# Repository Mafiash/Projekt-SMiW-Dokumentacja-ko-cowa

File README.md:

# Smart LED - Inteligentny Sysytem Oświetlenia LED

**Autor:** Mateusz Smuda
**Sekcja:** 10 
**Nr albumu:** 312441 
**Rok:** 2025 

## Opis Projektu
Projekt "Smart LED" to system automatycznego sterowania oświetleniem LED WS2812B opartym na mikrokontrolerze ESP32-WROOM-32E. System wykorzystuje zaawansowany radar obecności (LD2410C) zamiast tradycyjnych czujników PIR. Dodatkowo barwa światła dostosowuje się do temperatury otoczenia przy użyciu czujnika DHT22, a jasność świecenia jest regulowana automatycznie w zależności od jasności otoczenia za pomocą fotorezystora.

Układ zarządzany jest przez własny serwer WWW postawiony na ESP32, umożliwiający zdalne sterowanie z poziomu przeglądarki (telefon/komputer).

## Główne Funkcjonalności
- **Wykrywanie obecności:** Radar LD2410C (wykrywanie ruchu i bezruchu).
- **Adaptacja barwna:** Zmiana koloru LED w zależności od temperatury (Niebieski <20°C / Zielony / Czerwony >26°C).
- **Adaptacja jasności:** Automatyczne ściemnianie w nocy i rozjaśnianie w dzień.
- **Interfejs WWW:** Panel sterowania (HTML/JS) z podglądem parametrów na żywo.
- **Tryby pracy:** 
  - **AUTO:** Pełna automatyka sensorowa.
  - **MANUAL:** Ręczne ustawianie koloru (RGB) i jasności suwakiem.

## Wykorzystany Sprzęt
1. **Mikrokontroler:** ESP32-WROOM-32E
2. **Oświetlenie:** Taśma LED adresowalna WS2812B (60 diod)
3. **Sensor ruchu:** Radar HLK-LD2410C
4. **Sensor temp/wilg:** DHT22
5. **Sensor światła:** Moduł z fotorezystorem

## Technologie
- **Język:** C++ (Arduino IDE)
- **Web:** HTML, CSS, JavaScript
- **Biblioteki:** Adafruit NeoPixel, DHT Sensor Library, WiFi.h, WebServer.h

## Instrukcja Uruchomienia
1. Podłącz zasilanie 5V.
2. Połącz się z siecią WiFi.

3. Wpisz w przeglądarce adres IP urządzenia.

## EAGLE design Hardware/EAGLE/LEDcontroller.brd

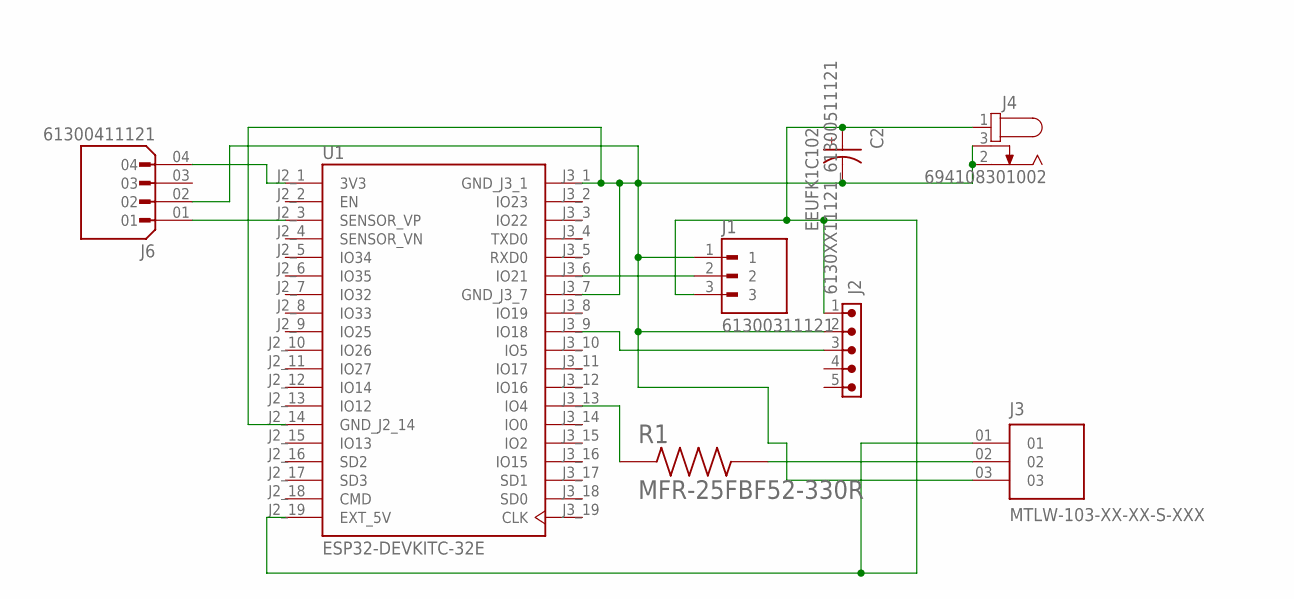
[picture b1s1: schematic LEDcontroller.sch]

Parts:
C2: EEUFK1C102; CAPPRD500W60D1000H1600
J1: 61300311121; WURTH_61300311121
J2: 6130XX11121_61300511121; 61300511121
J3: MTLW-103-XX-XX-S-XXX; SAMTEC_MTLW-103-XX-XX-S-XXX
J4: 694108301002
J6: 61300411121; WURTH_61300411121
R1: MFR-25FBF52-330R; RESAD1100W55L680D260
U1: ESP32-DEVKITC-32E; MODULE_ESP32-DEVKITC-32E

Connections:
GND: C2.N, J1.1, J2.2, J3.03, J4.2, J4.3, J6.02, U1.J2_14 (GND_J2_14), U1.J3_1 (GND_J3_1), U1.J3_7 (GND_J3_7)
unnamed: J2.3, U1.J3_9 (IO18)
unnamed: J6.04, U1.J2_1 (3V3)
unnamed: J1.2, U1.J3_6 (IO21)
unnamed: J3.02, R1.2
unnamed: J6.01, U1.J2_3 (SENSOR_VP)
unnamed: R1.1, U1.J3_13 (IO4)
VCC: C2.P, J1.3, J2.1, J3.01, J4.1, U1.J2_19 (EXT_5V)

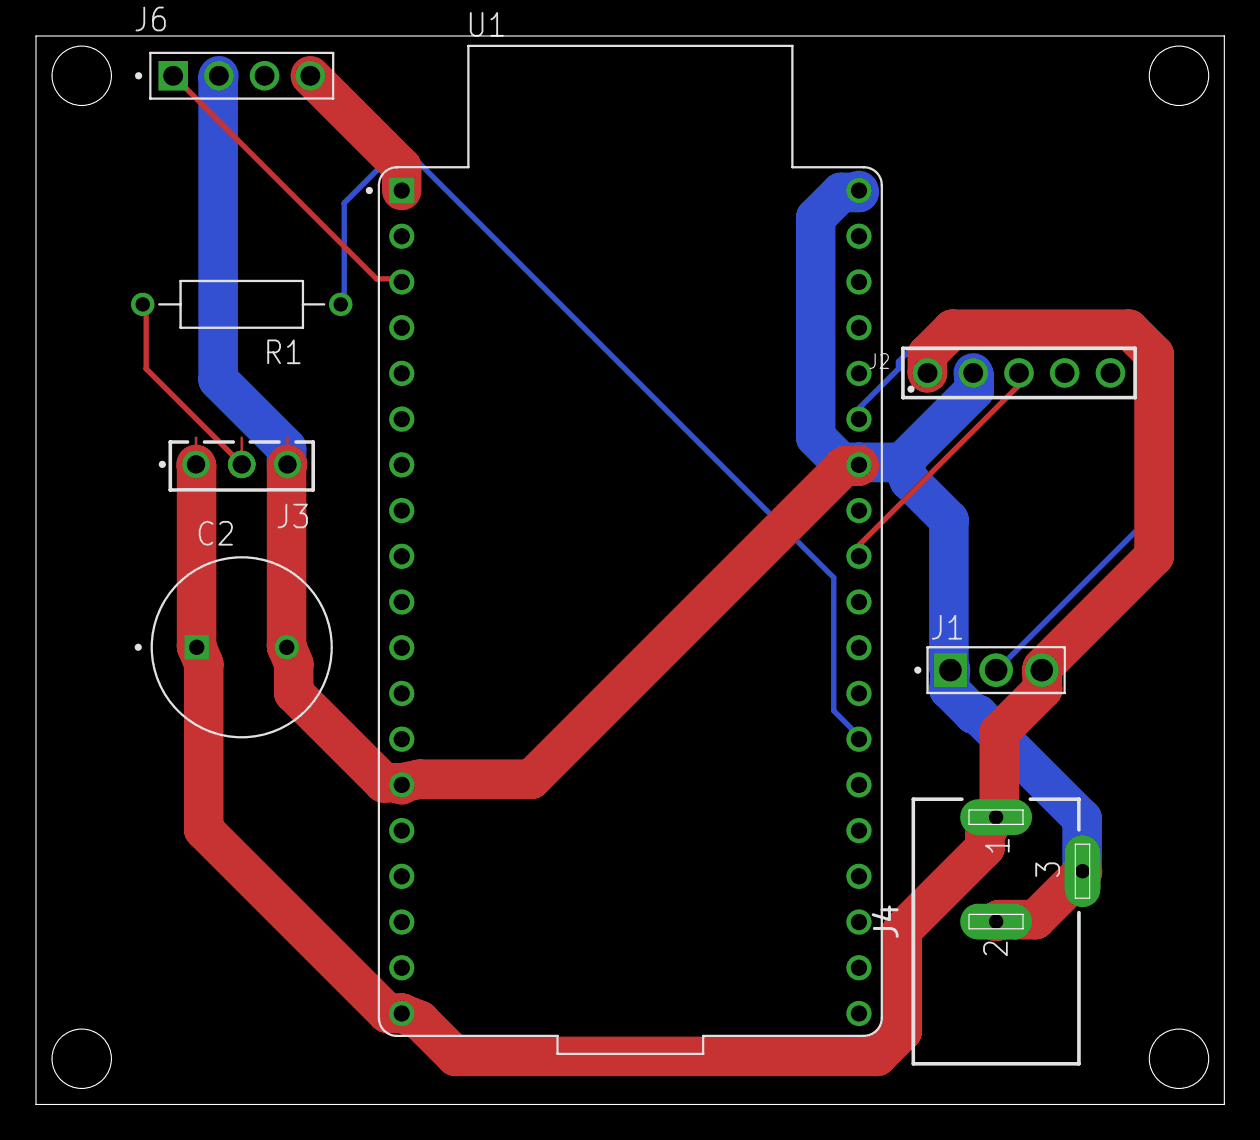
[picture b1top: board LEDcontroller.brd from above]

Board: 2 copper layers, 66.0 x 59.4 mm, 8 parts (0 on the bottom side), 8 nets.
